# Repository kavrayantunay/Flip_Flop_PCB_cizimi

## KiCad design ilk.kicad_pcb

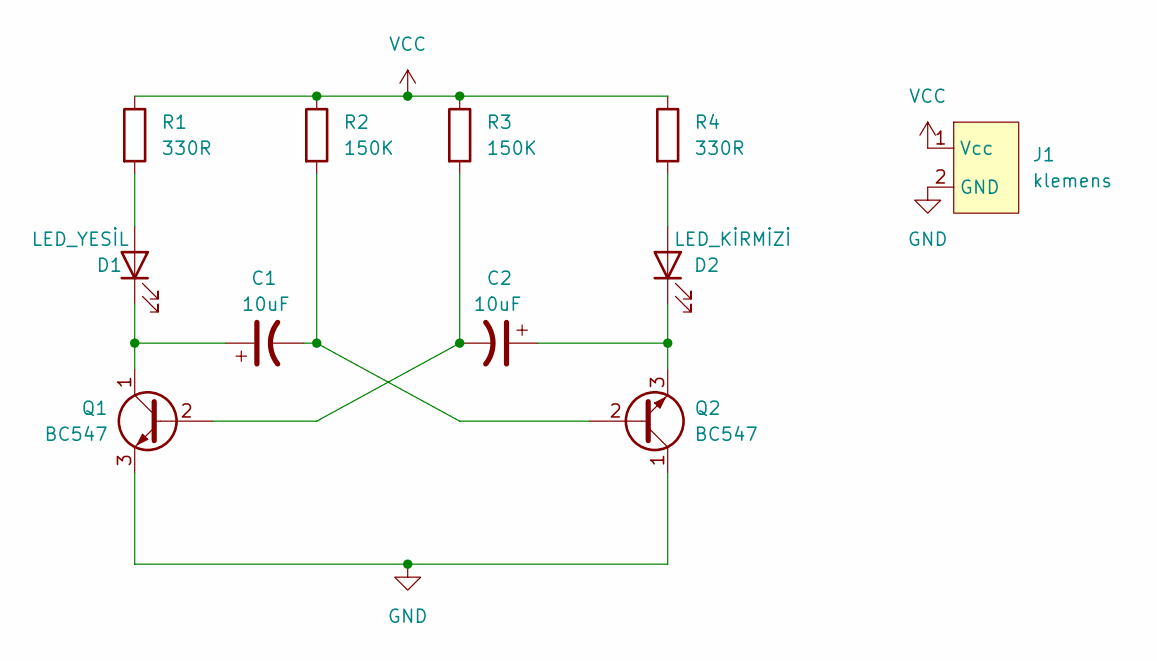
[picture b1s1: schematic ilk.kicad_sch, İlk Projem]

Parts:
C1, C2: 10uF; CP_Radial_D8.0mm_P2.50mm
D1: LED_YESİL; LED_D5.0mm
D2: LED_KİRMİZİ; LED_D5.0mm
J1: klemens
Q1, Q2: BC547; TO-92_Inline
R1, R4: 330R; R_Axial_DIN0207_L6.3mm_D2.5mm_P7.62mm_Horizontal
R2, R3: 150K; R_Axial_DIN0207_L6.3mm_D2.5mm_P7.62mm_Horizontal

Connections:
GND: J1.2 (GND), Q1.3 (E), Q2.1 (C)
unnamed: C1.1, D1.1 (K), Q1.1 (C)
unnamed: C1.2, Q2.2 (B), R2.2
unnamed: C2.1, D2.1 (K), Q2.3 (E)
unnamed: C2.2, Q1.2 (B), R3.2
unnamed: D1.2 (A), R1.2
unnamed: D2.2 (A), R4.2
VCC: J1.1 (Vcc), R1.1, R2.1, R3.1, R4.1

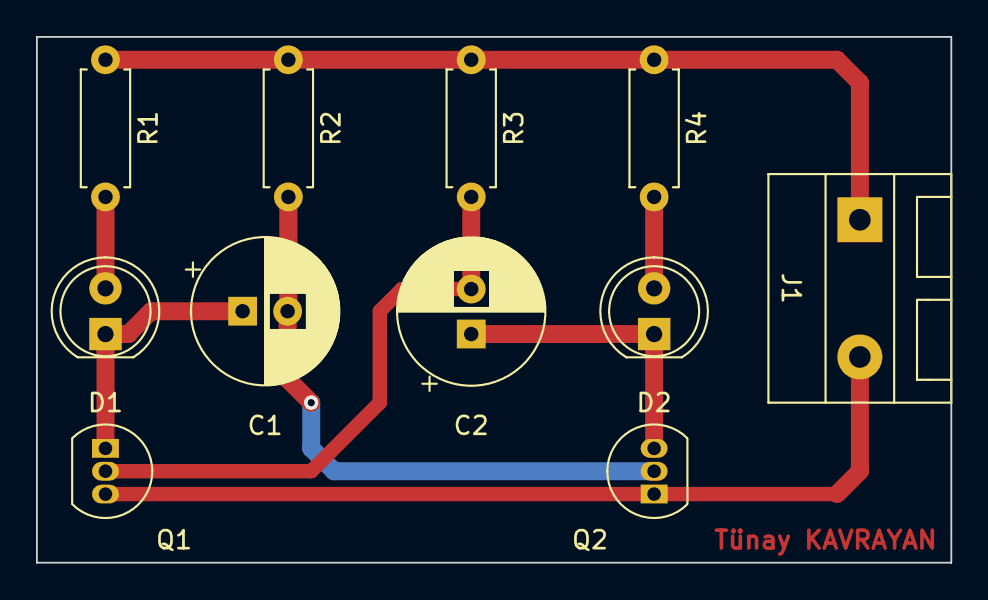
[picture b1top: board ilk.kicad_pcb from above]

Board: 2 copper layers, 50.8 x 29.2 mm, 11 parts (0 on the bottom side), 8 nets.

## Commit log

2022-10-01 Add files via upload
    Kicad programı ile çizilmiş flip flop devre kartı ve Gerber dosyaları
